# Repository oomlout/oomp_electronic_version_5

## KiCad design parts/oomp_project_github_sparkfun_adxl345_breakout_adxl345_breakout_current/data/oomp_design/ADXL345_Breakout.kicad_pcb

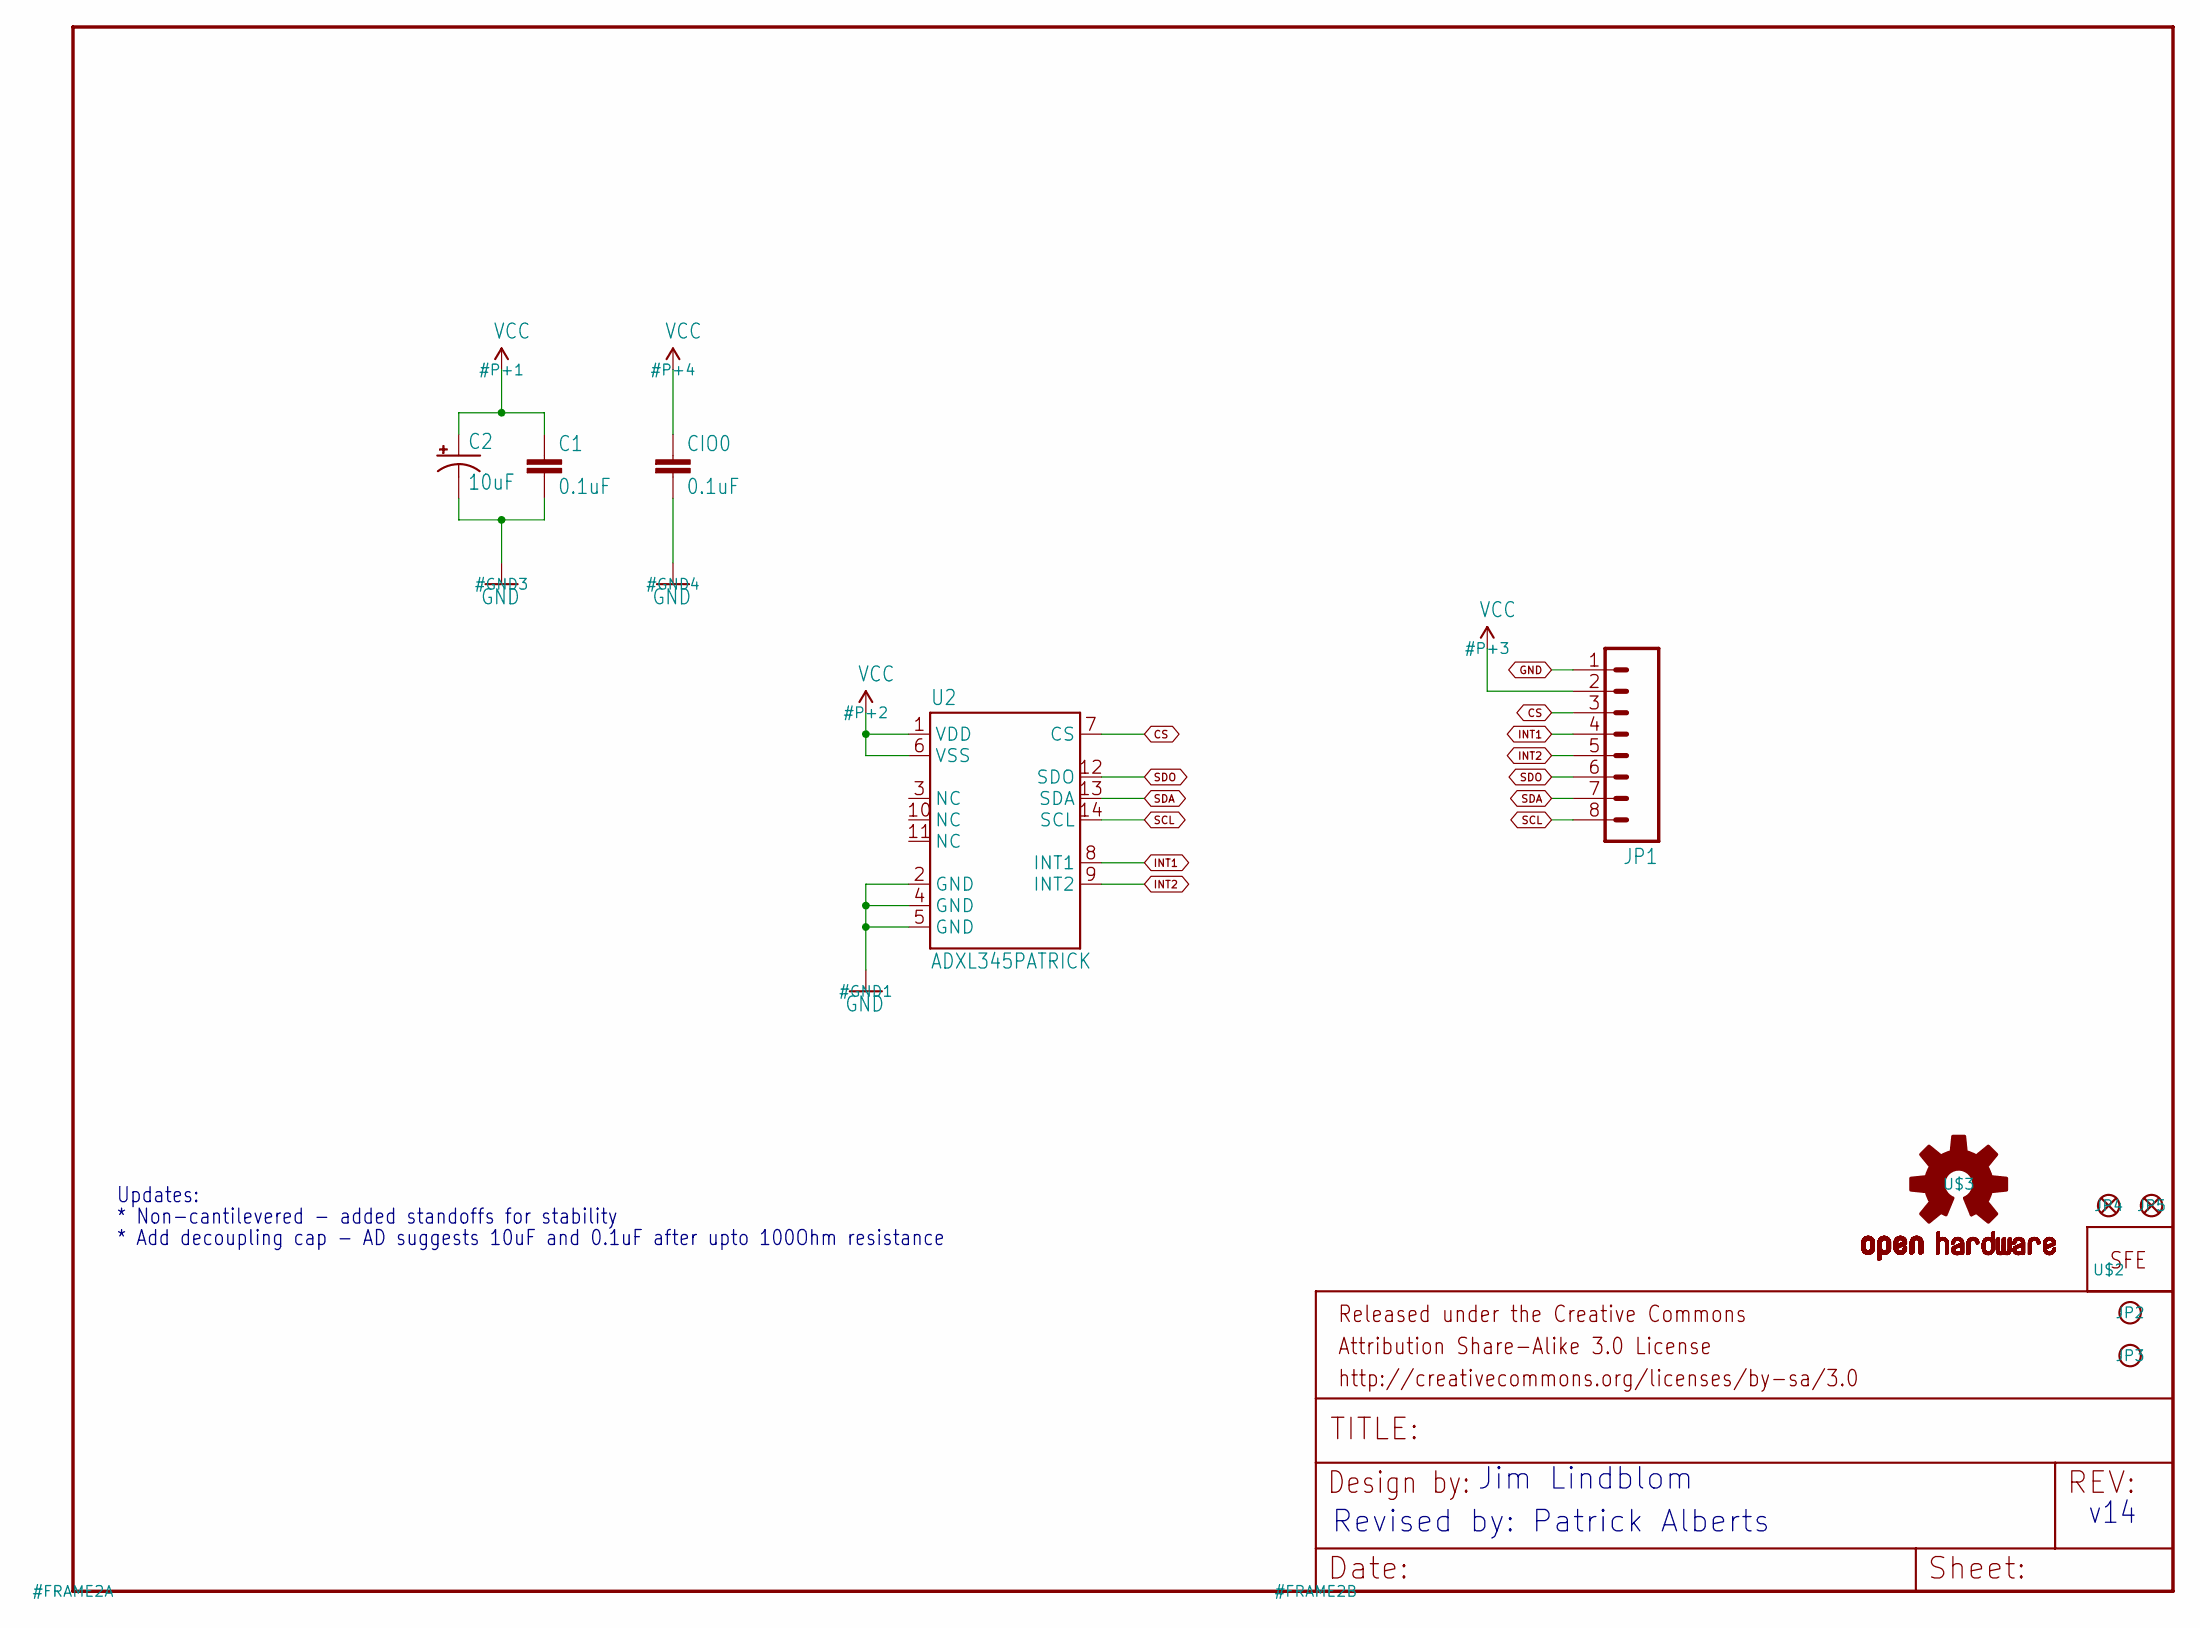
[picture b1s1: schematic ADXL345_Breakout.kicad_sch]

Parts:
C1: 0.1uF; 0603-CAP
C2: 10uF; EIA3216
CIO0: 0.1uF; 0603-CAP
JP1: M08; 1X08
JP2, JP3: STAND-OFF
JP4, JP5: FIDUCIAL1X2; FIDUCIAL-1X2
U2: ADXL345PATRICK; LGA14_1_1_PATRICK
U$2: LOGO-SFENEW; SFE-NEW-WEBLOGO
U$3: OSHW-LOGOS; OSHW-LOGO-S

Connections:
CS: JP1.3, U2.7 (CS)
GND: C1.2, C2.C (-), CIO0.2, JP1.1, U2.2 (GND), U2.4 (GND), U2.5 (GND)
INT1: JP1.4, U2.8 (INT1)
INT2: JP1.5, U2.9 (INT2)
SCL: JP1.8, U2.14 (SCL)
SDA: JP1.7, U2.13 (SDA)
SDO: JP1.6, U2.12 (SDO)
VCC: C1.1, C2.A (+), CIO0.1, JP1.2, U2.1 (VDD), U2.6 (VSS)

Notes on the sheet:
Revised by: Patrick Alberts
* Non-cantilevered - added standoffs for stability
Jim Lindblom
Updates:
* Add decoupling cap - AD suggests 10uF and 0.1uF after upto 100Ohm resistance
v14

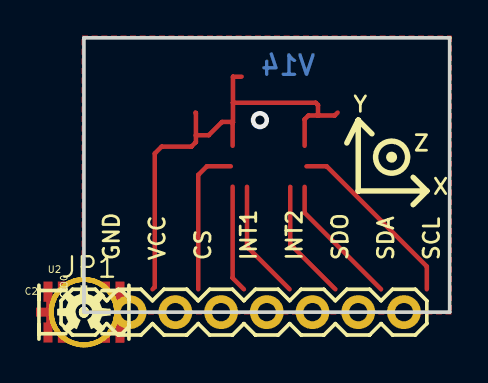
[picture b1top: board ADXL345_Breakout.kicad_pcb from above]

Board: 2 copper layers, 20.3 x 15.2 mm, 11 parts (1 on the bottom side), 8 nets.

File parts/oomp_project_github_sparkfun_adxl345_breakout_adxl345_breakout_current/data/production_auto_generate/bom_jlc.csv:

Comment,Designator,Footprint,LCSC Part #
,JP1,ADXL345_Breakout-import-fps:1X08,C492421
0.1uF,"C1,CIO0",ADXL345_Breakout-import-fps:0603-CAP,C14663
10uF,C2,ADXL345_Breakout-import-fps:EIA3216,
ADXL345PATRICK,U2,ADXL345_Breakout-import-fps:LGA14_1_1_PATRICK,
FIDUCIAL1X2,"JP4,JP5",ADXL345_Breakout-import-fps:FIDUCIAL-1X2,
LOGO-SFENEW,U$2,ADXL345_Breakout-import-fps:SFE-NEW-WEBLOGO,
OSHW-LOGOS,U$3,ADXL345_Breakout-import-fps:OSHW-LOGO-S,

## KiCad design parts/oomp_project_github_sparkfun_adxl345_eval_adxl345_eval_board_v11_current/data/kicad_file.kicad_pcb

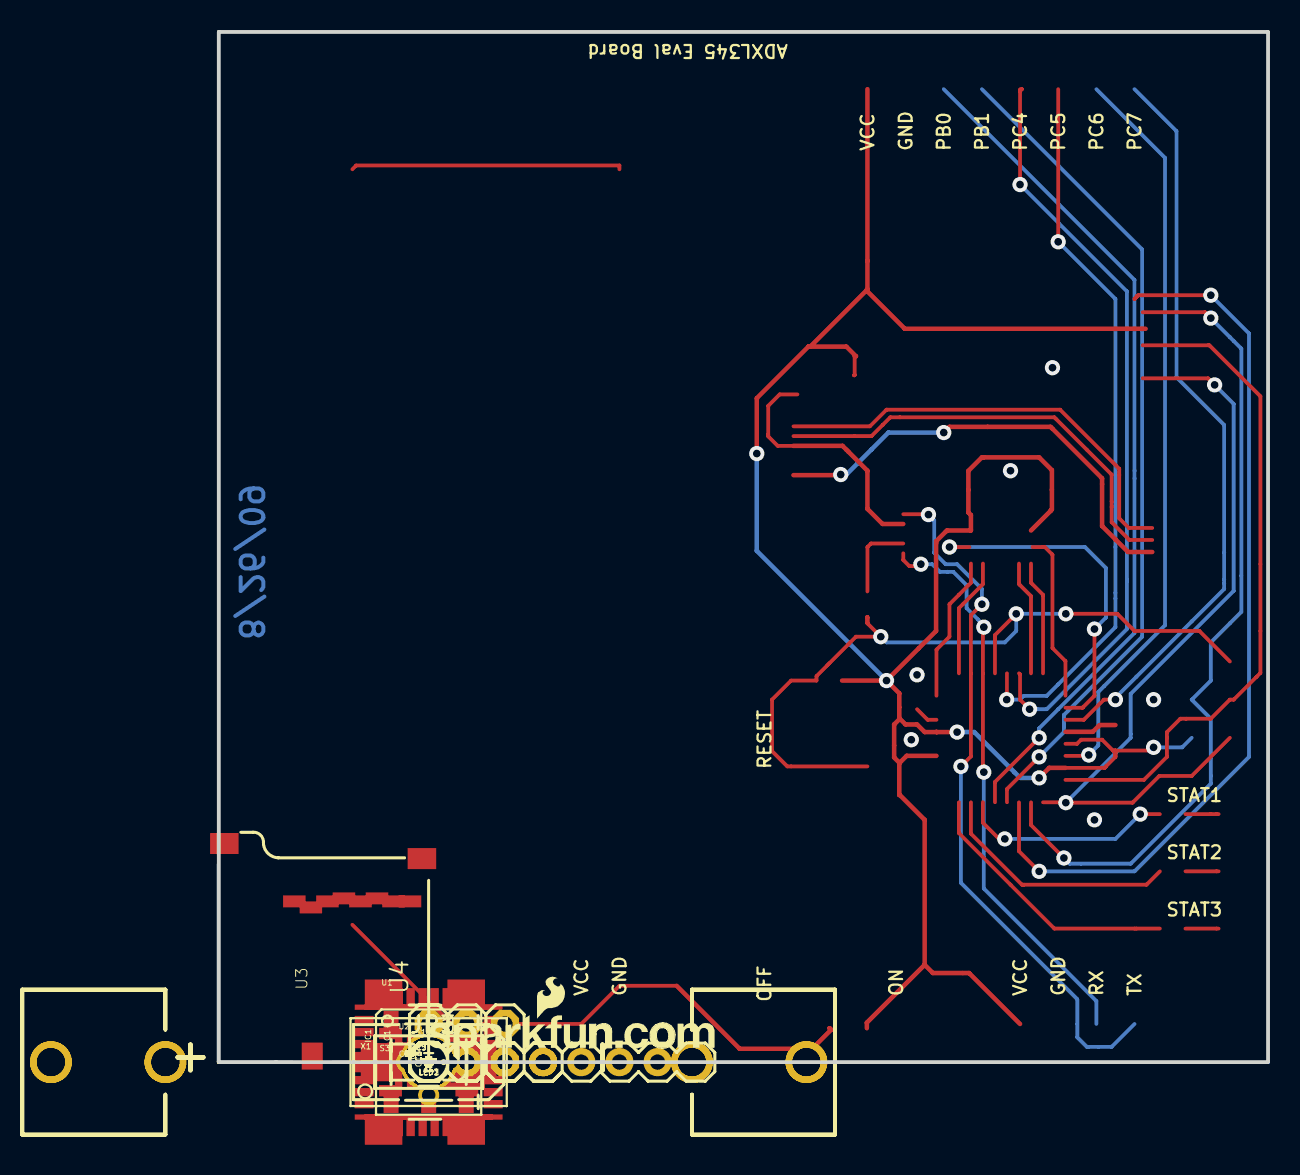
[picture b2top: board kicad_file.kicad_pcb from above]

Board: 2 copper layers, 69.9 x 68.6 mm, 38 parts (0 on the bottom side), 34 nets.

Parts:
BAT1, BAT2: AA Battery; ACCEL_SCK
C1: 10uF; EIA3216
C3, C5, C6, C7, C8, C9, C10, C12: 0.1uF; 0603-CAP
C4: 1uF; 0805
C11: 4.7uF; EIA7343
IC1: FT232RLSSOP; SSOP28DB
JP1: 1X08
JP2: 1X04
JP3: 1X02
LED1, LED2, LED3: LED-0603
R3: 10k; 0603-RES
R6, R7, R8: 330; 0603-RES
S1: TACTILE_SWITCH_SMD
S3: Power Switch; AYZ0202
U1: ATMEGA168; TQFP32-08
U2: ADXL345; LGA14
U3: USD-SOCKETNEW; MICRO-SD-SOCKET-PP
U4: AVR_SPI_PRG_6PTH; 2X3
U$1: LOGO-SFENEW; SFE-NEW-WEBLOGO
U$2, U$3: FIDUCIAL1X2; FIDUCIAL-1X2
U$4, U$5, U$6, U$7: STAND-OFF
X1: USBSMD; USB-MINIB

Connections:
ACCEL_CS: U1.23, U2.7
ACCEL_DI: U1.25, U2.13
ACCEL_DO: U1.26, U2.12
ACCEL_INT1: U1.1, U2.8
ACCEL_INT2: U1.32, U2.9
ACCEL_SCK: U1.24, U2.14
CS: U1.14, U3.2
DTR: C12.1, IC1.2
GND: BAT2.GND@1, C1.C, C3.2, C4.1, C5.1, C6.1, C7.1, C8.1, C9.1, C10.1, C11.C, IC1.7, IC1.18, IC1.21, IC1.25, IC1.26, JP1.2, JP2.2, JP3.2, LED1.C, LED2.C, LED3.C, S1.1, S1.2, U1.3, U1.5, U1.21, U2.2, U2.4, U2.5, U2.10, U3.6, U3.GND1, U3.GND2, U4.6, X1.GND
MISO: U1.16, U3.7, U4.1
MOSI: U1.15, U3.3, U4.4
unnamed: LED1.A, R6.1
unnamed: BAT1.GND@1, BAT2.PWR@1
unnamed: LED2.A, R7.1
unnamed: IC1.20, X1.VBUS
unnamed: LED3.A, R8.1
unnamed: IC1.16, X1.D-
unnamed: IC1.15, X1.D+
unnamed: C10.2, IC1.4, IC1.17
PB0: JP1.3, U1.12
PB1: JP1.4, U1.13
PC4: JP1.5, U1.27
PC5: JP1.6, U1.28
PC6: JP1.7, U1.19
PC7: JP1.8, U1.22
RAW: BAT1.PWR@1, JP3.1, S3.2
RESET: C12.2, R3.1, S1.3, S1.4, U1.29, U4.5
RX-I: IC1.1, JP2.3, U1.30
SCK: U1.17, U3.5, U4.3
STAT1: R6.2, U1.11
STAT2: R7.2, U1.10
STAT3: R8.2, U1.9
TX-O: IC1.5, JP2.4, U1.31
VCC: C1.A, C3.1, C4.2, C5.2, C6.2, C7.2, C8.2, C9.2, C11.A, JP1.1, JP2.1, R3.2, S3.1, U1.4, U1.6, U1.18, U1.20, U2.1, U2.6, U3.4, U4.2

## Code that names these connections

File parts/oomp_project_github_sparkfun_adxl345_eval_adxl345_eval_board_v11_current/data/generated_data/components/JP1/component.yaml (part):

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      units: mm
    layers:
    - '*.Cu'
    net: PB0
    net_number: null
    pin_function: null
    pin_type: null
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      units: mm
    layers:
    - '*.Cu'
    net: PB1
    net_number: null
    pin_function: null
    pin_type: null
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      units: mm
    layers:
    - '*.Cu'
    net: PC4
    net_number: null
    pin_function: null
    pin_type: null
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      units: mm
    layers:
    - '*.Cu'
    net: PC5
    net_number: null
    pin_function: null
    pin_type: null
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      units: mm
    layers:
    - '*.Cu'
    net: PC6
    net_number: null
    pin_function: null
    pin_type: null
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      units: mm
    layers:
    - '*.Cu'
    net: PC7
    net_number: null
    pin_function: null
    pin_type: null
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  - pin_or_pad_number: '3'
    schematic_nets: []
    pcb_nets:
    - PB0
    status: incomplete
  - pin_or_pad_number: '4'
    schematic_nets: []
    pcb_nets:
    - PB1
    status: incomplete
  - pin_or_pad_number: '5'
    schematic_nets: []
    pcb_nets:
    - PC4
    status: incomplete
  - pin_or_pad_number: '6'
    schematic_nets: []
    pcb_nets:
    - PC5
    status: incomplete
  - pin_or_pad_number: '7'
    schematic_nets: []
    pcb_nets:
    - PC6
    status: incomplete
  - pin_or_pad_number: '8'
    schematic_nets: []
    pcb_nets:
    - PC7
    status: incomplete
  agree_count: 0
  disagree_count: 0
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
